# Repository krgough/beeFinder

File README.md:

# beeFinder

This device consists of:
- An array of 5x5 LEDs used as a display
- An RFM69HW 868MHz radio
- Arduino Pro Mini used as the controller

We have 2 modes of operation:
1) Display Name of Owner - Name scrolls from left to right.
2) Transmit a broadcast to other devices on 868MHz network.  Each column of LEDs is a user and the column leds correspond to the RSSI for that device.  The column for this device has only the lower LED lit

Mode selection is done using the SCAN/NAME switch.

# config.h
Create a config.h file with the radio encryption key.  This must be exactly 16 chars e.g.
```
#define ENCRYPTKEY    "sampleEncryptKey"
```

# vs-code
Install the arduino extension
Install arduino-cli
```
brew install arduino-cli
```
*** IMPORTANT: Restart vs-code

Use ```which arduino-cli``` to find the location of your executable
Set these vs-code settings...
arduino.path = <folder from 'which arduino-cli'>
arduino.command_path = arduino-cli

Set the script name in ardiono.json  

Typical arduino.json:
```
{
    "port": "/dev/tty.usbserial-AQ034BWC",
    "configuration": "cpu=16MHzatmega328",
    "board": "arduino:avr:pro",
    "sketch": "bee_finder_firmware/bee_finder/bee_finder.ino"
}
```

# Programming
- Connect GND, Tx, Rx
- Connect RTS from FTDI cable to DTR on the beekeeper device to allow it to set programming mode

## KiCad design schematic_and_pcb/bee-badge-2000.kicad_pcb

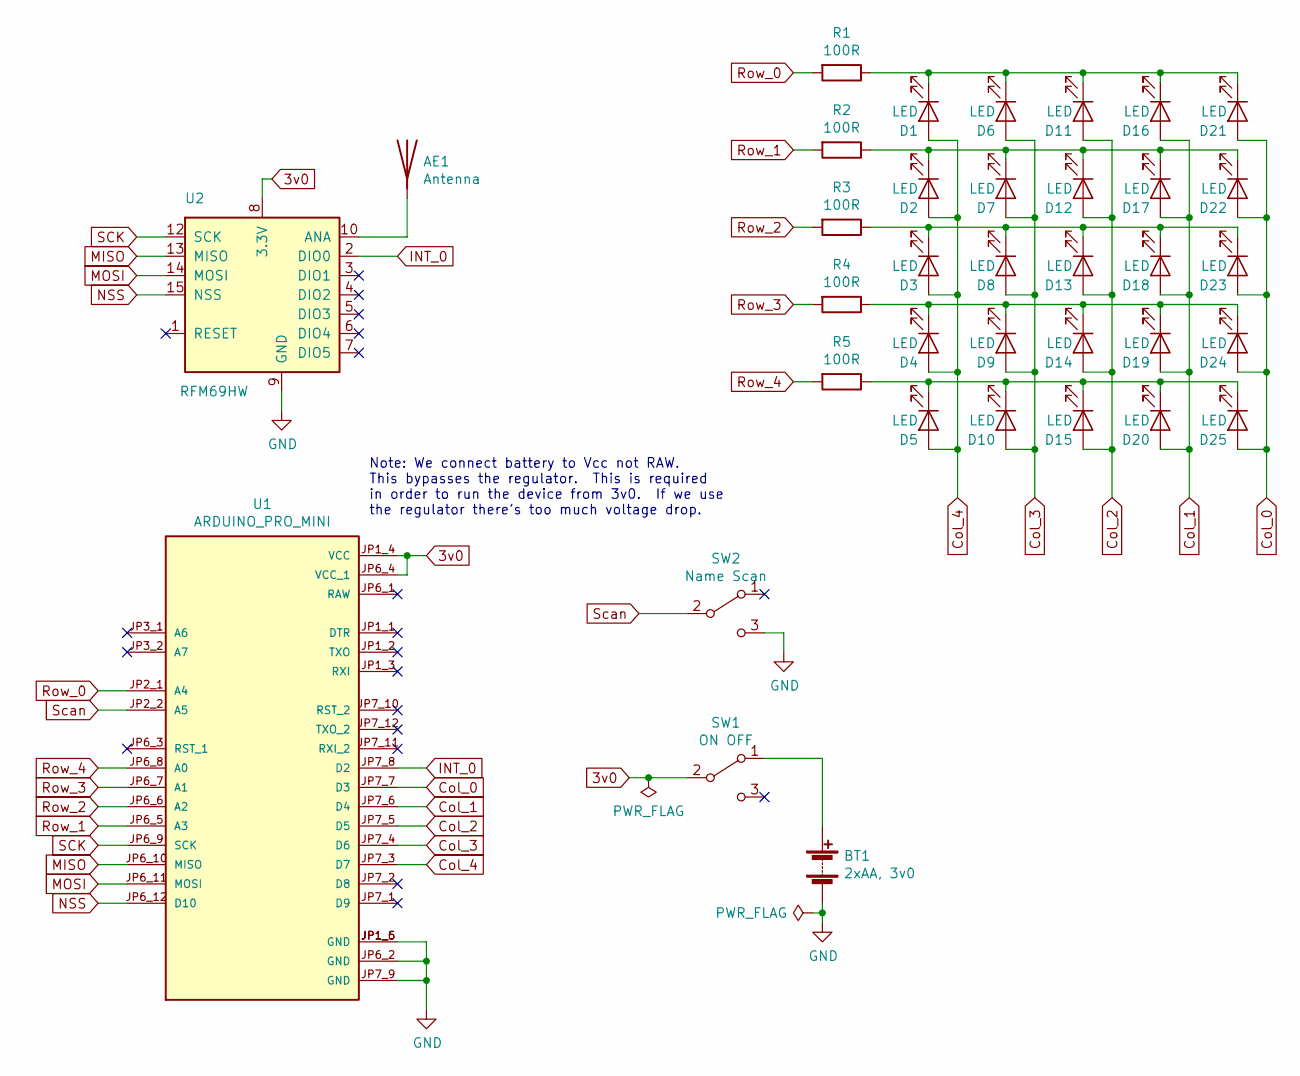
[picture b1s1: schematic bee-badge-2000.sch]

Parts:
AE1: Antenna; ti-868-antenna-meander
BT1: 2xAA, 3v0; 2xAA_Battery_Holder_PCB_Mount
D1, D2, D3, D4, D5, D6, D7, D8, D9, D10, D11, D12, D13, D14, D15, D16, D17, D18, D19, D20, D21, D22, D23, D24, D25: LED; LED_D5.0mm
R1, R2, R3, R4, R5: 100R; R_Axial_DIN0207_L6.3mm_D2.5mm_P10.16mm_Horizontal
SW1: ON OFF; SS12D00G4_spdt
SW2: Name Scan; SS12D00G4_spdt
U1: ARDUINO_PRO_MINI; MODULE_ARDUINO_PRO_MINI_CHINA; PARTREV N/A
U2: RFM69HW; HOPERF_RFM69HW

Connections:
3v0: SW1.2 (B), U1.JP1_4 (VCC), U1.JP6_4 (VCC_1), U2.8 (3.3V)
Col_0: D21.2 (A), D22.2 (A), D23.2 (A), D24.2 (A), D25.2 (A), U1.JP7_7 (D3)
Col_1: D16.2 (A), D17.2 (A), D18.2 (A), D19.2 (A), D20.2 (A), U1.JP7_6 (D4)
Col_2: D11.2 (A), D12.2 (A), D13.2 (A), D14.2 (A), D15.2 (A), U1.JP7_5 (D5)
Col_3: D6.2 (A), D7.2 (A), D8.2 (A), D9.2 (A), D10.2 (A), U1.JP7_4 (D6)
Col_4: D1.2 (A), D2.2 (A), D3.2 (A), D4.2 (A), D5.2 (A), U1.JP7_3 (D7)
GND: BT1.2 (-), SW2.3 (C), U1.JP1_5 (GND), U1.JP1_6 (GND), U1.JP6_2 (GND), U1.JP7_9 (GND), U2.9 (GND), U2.11 (GND)
INT_0: U1.JP7_8 (D2), U2.2 (DIO0)
MISO: U1.JP6_10 (MISO), U2.13 (MISO)
MOSI: U1.JP6_11 (MOSI), U2.14 (MOSI)
NSS: U1.JP6_12 (D10), U2.15 (NSS)
unnamed: AE1.1, U2.10 (ANA)
unnamed: BT1.1 (+), SW1.1 (A)
unnamed: D1.1 (K), D6.1 (K), D11.1 (K), D16.1 (K), D21.1 (K), R1.1
unnamed: D5.1 (K), D10.1 (K), D15.1 (K), D20.1 (K), D25.1 (K), R5.1
unnamed: D2.1 (K), D7.1 (K), D12.1 (K), D17.1 (K), D22.1 (K), R2.1
unnamed: D3.1 (K), D8.1 (K), D13.1 (K), D18.1 (K), D23.1 (K), R3.1
unnamed: D4.1 (K), D9.1 (K), D14.1 (K), D19.1 (K), D24.1 (K), R4.1
Row_0: R1.2, U1.JP2_1 (A4)
Row_1: R2.2, U1.JP6_5 (A3)
Row_2: R3.2, U1.JP6_6 (A2)
Row_3: R4.2, U1.JP6_7 (A1)
Row_4: R5.2, U1.JP6_8 (A0)
SCK: U1.JP6_9 (SCK), U2.12 (SCK)
Scan: SW2.2 (B), U1.JP2_2 (A5)

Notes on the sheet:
Note: We connect battery to Vcc not RAW. This bypasses the regulator. This is required in order to run the device from 3v0. If we use the regulator there’s too much voltage drop.

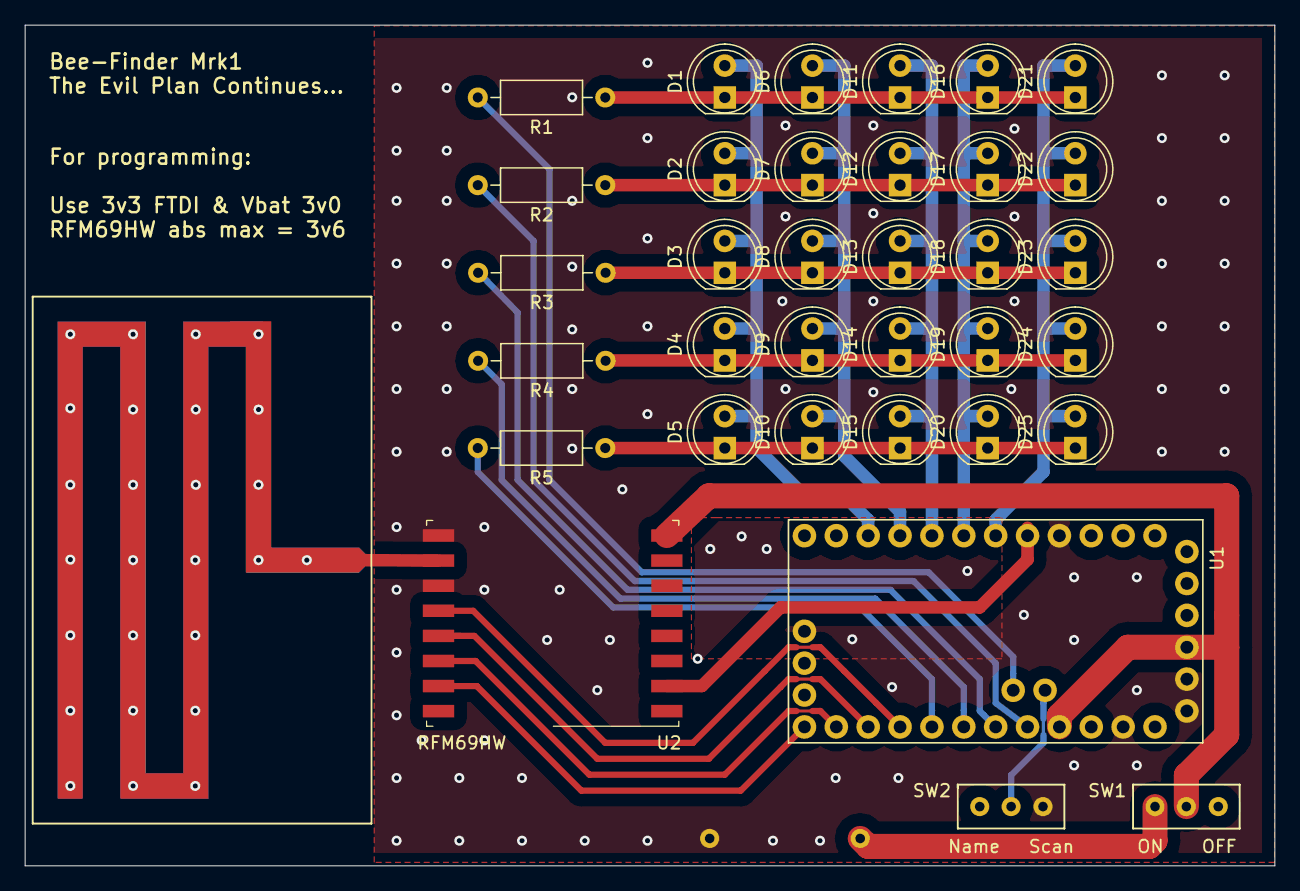
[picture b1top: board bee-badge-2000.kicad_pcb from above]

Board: 2 copper layers, 99.6 x 67.0 mm, 36 parts (1 on the bottom side), 25 nets.

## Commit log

2022-12-23 Handle 'space' in a better way
2022-12-23 Fixed frequency of arduino clock
2025-11-15 adding pdf of the schematic
